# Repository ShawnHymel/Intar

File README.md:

Intar
=====

Open source laser tag system.

Repository Contents
-------------------

* **/Hardware** - Eagle design files (.brd, .sch)
* **/Libraries** - Libraries for use with the ZX Distance and Gesture Sensor

Documentation
-------------

Version History
---------------

* [H_0.0_L_0.2.0](https://github.com/ShawnHymel/Intar/tree/H_0.0_L_0.2.0) - Added ATtiny84 support to library
* [H_0.0_L_0.1.0](https://github.com/ShawnHymel/Intar/tree/H_0.0_L_0.1.0) - First prototype of a working IR library

License Information
-------------------

This product is _**open source**_! 

Please review the LICENSE.md file for license information. 

Distributed as-is; no warranty is given.

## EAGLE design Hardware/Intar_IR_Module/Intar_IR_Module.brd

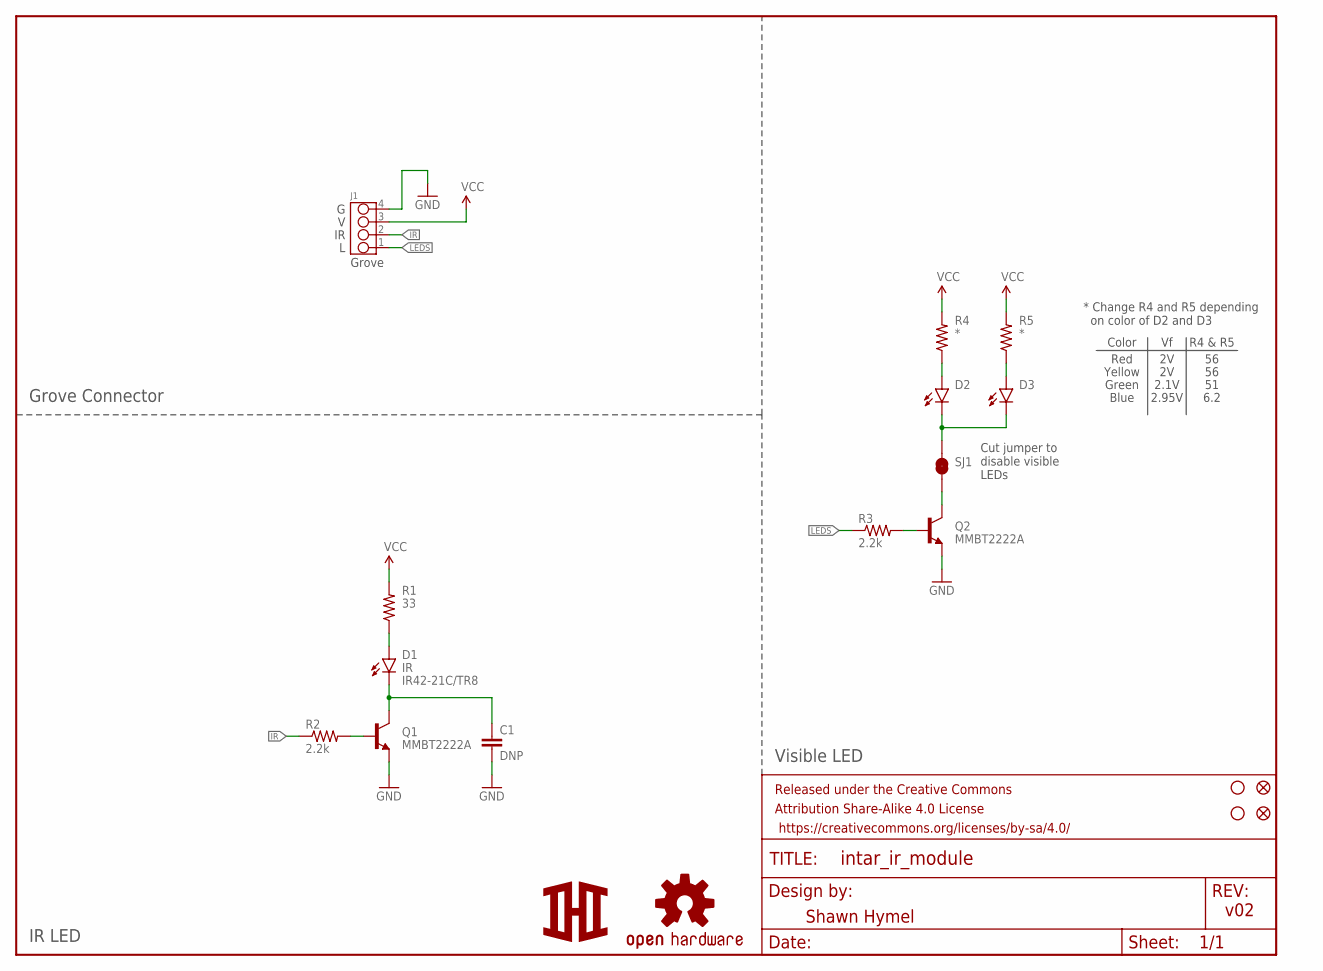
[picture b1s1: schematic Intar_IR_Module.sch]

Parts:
C1: DNP; 0603-CAP
D1: IR; IR42-21C/TR8
D2, D3: LED0603; LED-0603
FID1, FID2: FIDUCIAL1X2; FIDUCIAL-1X2
FRAME1: FRAME-LETTER; CREATIVE_COMMONS
J1: GROVE-4P-2.0-3470130P1; 4P-2.0
LOGO1: OSHW-LOGOS; OSHW-LOGO-S
Q1, Q2: MMBT2222A; SOT23-3
R1: 33; 0603-RES
R2, R3: 2.2k; 0603-RES
R4, R5: *; 0603-RES
SJ1: JUMPER-PAD-2-NC_BY_TRACE; PAD-JUMPER-2-NC_BY_TRACE_YES_SILK
STANDOFF1, STANDOFF2: STAND-OFF
U$1: LOGOSM; LOGO_SM

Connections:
GND: C1.2, J1.4, Q1.2 (E), Q2.2 (E)
IR: J1.2, R2.1
LEDS: J1.1, R3.1
unnamed: Q1.1 (B), R2.2
unnamed: D1.A, R1.1
unnamed: C1.1, D1.C, Q1.3 (C)
unnamed: D2.C, D3.C, SJ1.2
unnamed: Q2.1 (B), R3.2
unnamed: D2.A, R4.1
unnamed: D3.A, R5.1
unnamed: Q2.3 (C), SJ1.1
VCC: J1.3, R1.2, R4.2, R5.2

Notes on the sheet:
Shawn Hymel
v02
Grove
Cut jumper to disable visible LEDs
* Change R4 and R5 depending on color of D2 and D3
Color
R4 & R5
Red
Grove Connector
IR LED
Visible LED
Yellow
Green
2.1V
Blue
2.95V
6.2

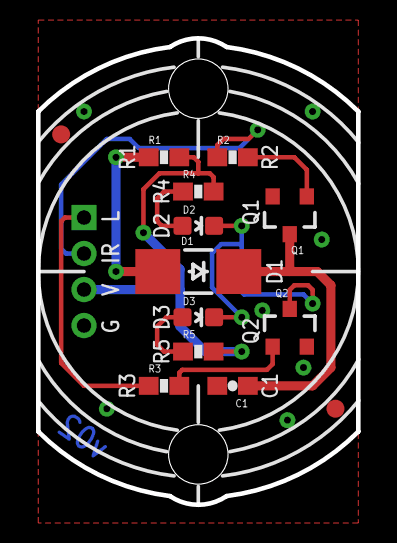
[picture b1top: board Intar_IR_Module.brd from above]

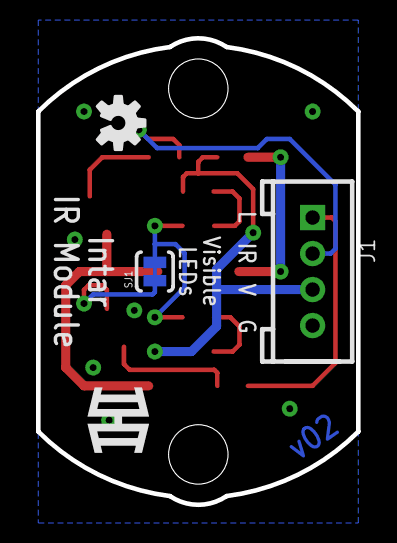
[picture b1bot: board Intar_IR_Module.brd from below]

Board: 2 copper layers, 17.8 x 25.9 mm, 20 parts (4 on the bottom side), 12 nets.

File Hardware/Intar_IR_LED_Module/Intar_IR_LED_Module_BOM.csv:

"Qty";"Value";"Device";"Package";"Parts";"Description";"MFG_NAME";"PROD_ID";"VALUE";
"2";"";"LED0603";"LED-0603";"D2, D3";"LEDs";"";"";"";
"2";"*";"RESISTOR0603-RES";"0603-RES";"R4, R5";"Resistor";"";"";"";
"1";"10nF";"10NF/10000PF-50V-10%(0603)";"0603-CAP";"C1";"CAP-00867";"";"CAP-00867";"10nF";
"2";"2.2k";"2.2KOHM-1/10W-1%(0603)";"0603-RES";"R2, R3";"RES-08272";"";"RES-08272";"2.2k";
"1";"30?";"RESISTOR0603-RES";"0603-RES";"R1";"Resistor";"";"";"";
"2";"FIDUCIAL1X2";"FIDUCIAL1X2";"FIDUCIAL-1X2";"FID1, FID2";"Fiducial Alignment Points";"";"";"";
"1";"FRAME-LETTER";"FRAME-LETTER";"CREATIVE_COMMONS";"FRAME1";"Schematic Frame";"";"";"";
"1";"GROVE-4P-2.0-3470130P1";"GROVE-4P-2.0-3470130P1";"4P-2.0";"J1";"";"";"";"";
"1";"IR";"LEDIR42-21C/TR8";"IR42-21C/TR8";"D1";"";"IR42-21C/TR8";"";"";
"1";"JUMPER-PAD-2-NC_BY_TRACE";"JUMPER-PAD-2-NC_BY_TRACE";"PAD-JUMPER-2-NC_BY_TRACE_YES_SILK";"SJ1";"";"";"";"";
"2";"MMBT2222A";"TRANSISTOR_NPNMMBT2222A";"SOT23-3";"Q1, Q2";"Generic NPN BJT";"";"TRANS-08049";"MMBT2222A";
"1";"OSHW-LOGOS";"OSHW-LOGOS";"OSHW-LOGO-S";"LOGO1";"Open Source Hardware Logo";"";"";"";
"2";"STAND-OFF";"STAND-OFF";"STAND-OFF";"STANDOFF1, STANDOFF2";"#4 Stand Off";"";"";"";

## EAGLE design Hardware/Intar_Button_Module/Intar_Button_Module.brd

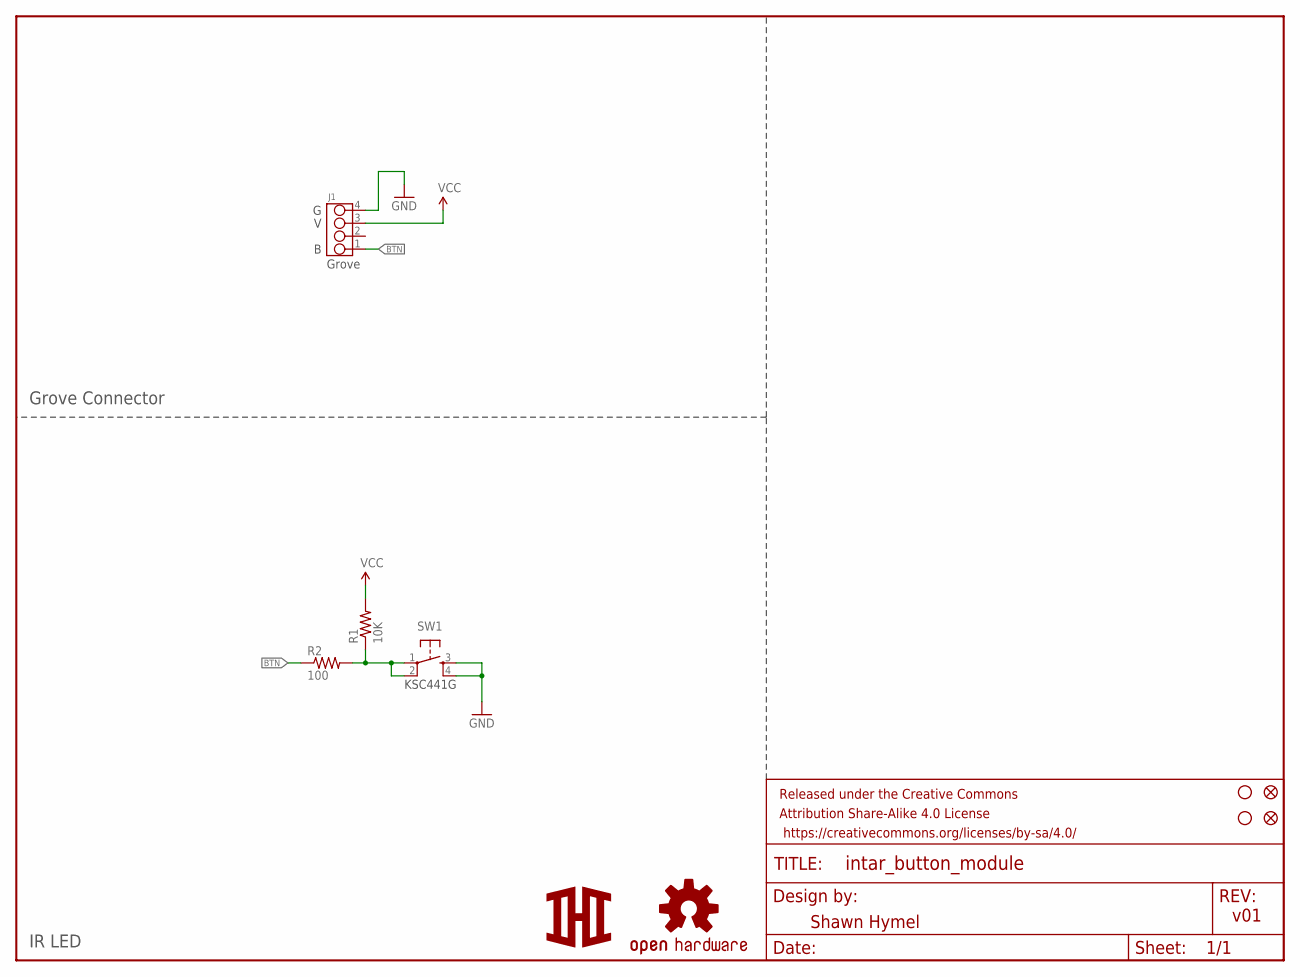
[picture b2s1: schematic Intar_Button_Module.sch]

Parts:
FID1, FID2: FIDUCIAL1X2; FIDUCIAL-1X2
FRAME1: FRAME-LETTER; CREATIVE_COMMONS
J1: GROVE-4P-2.0-3470130P1; 4P-2.0
LOGO1: OSHW-LOGOS; OSHW-LOGO-S
R1: 10K; 0603-RES
R2: 100; 0603-RES
STANDOFF1, STANDOFF2: STAND-OFF
SW1: SWITCH_MOMENTARY; KSCXXXG
U$1: LOGOSM; LOGO_SM

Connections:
BTN: J1.1, R2.1
GND: J1.4, SW1.3, SW1.4
unnamed: R1.1, R2.2, SW1.1, SW1.2
VCC: J1.3, R1.2

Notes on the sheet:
Shawn Hymel
v01
Grove
KSC441G
Grove Connector
IR LED

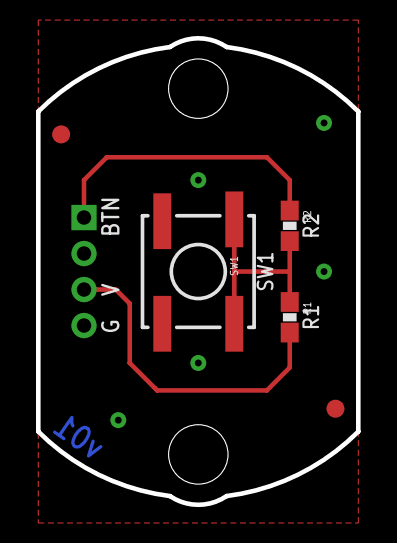
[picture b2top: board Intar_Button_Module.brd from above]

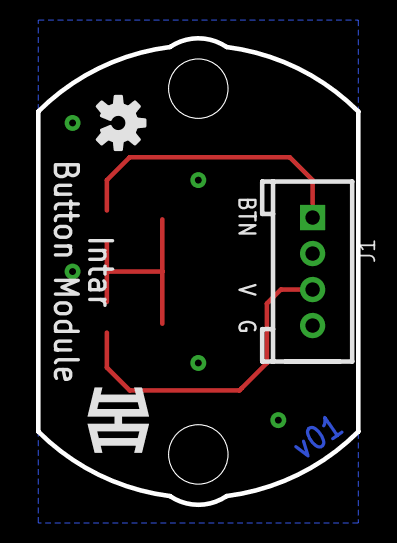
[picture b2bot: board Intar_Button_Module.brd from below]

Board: 2 copper layers, 17.8 x 25.9 mm, 11 parts (3 on the bottom side), 4 nets.

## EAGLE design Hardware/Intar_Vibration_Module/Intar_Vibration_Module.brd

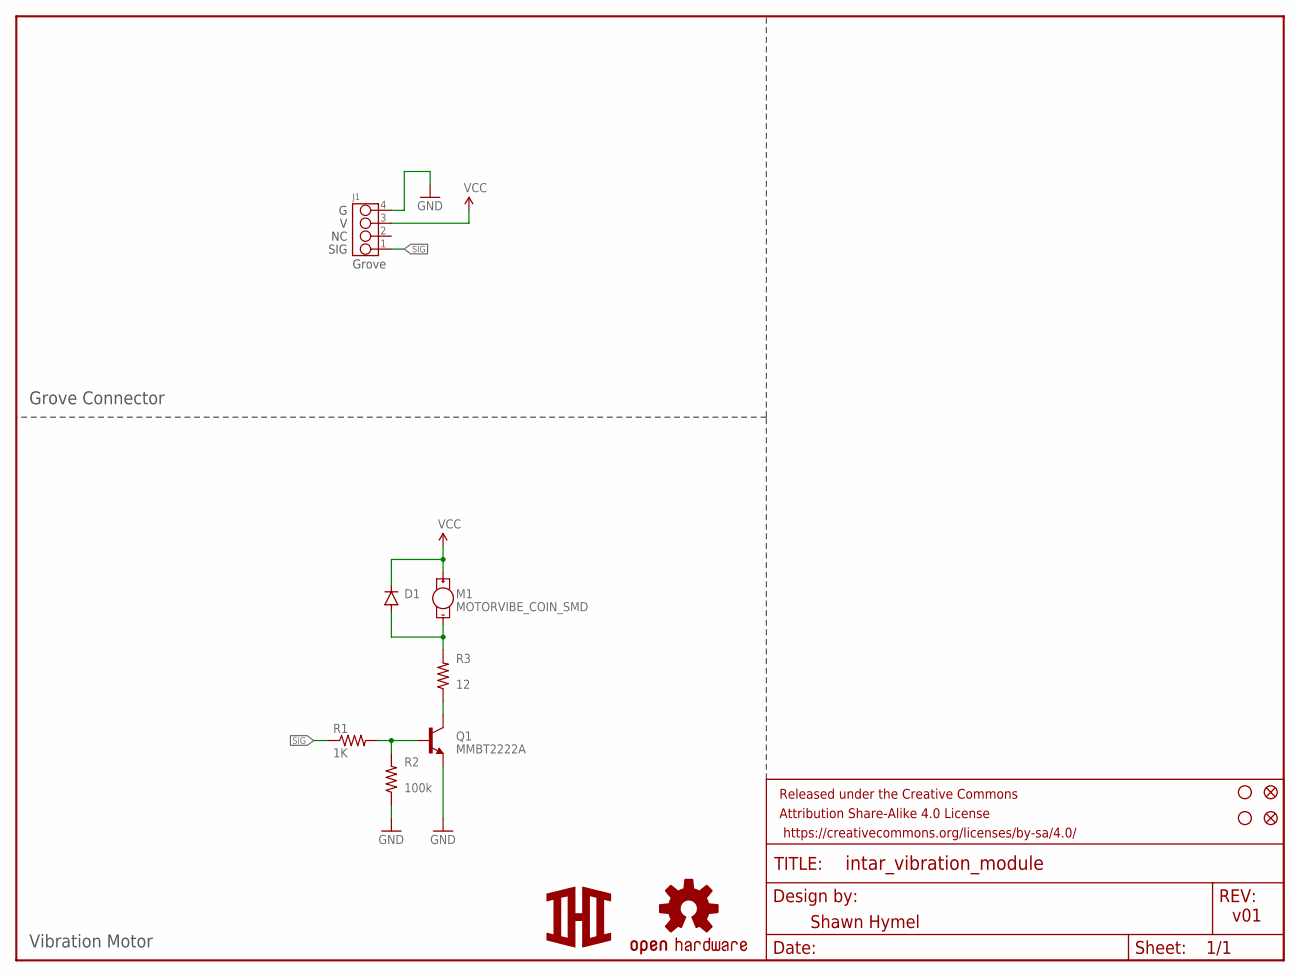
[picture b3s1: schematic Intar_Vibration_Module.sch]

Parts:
D1: 250mA/100V; SOD-323
FID1, FID2: FIDUCIAL1X2; FIDUCIAL-1X2
FRAME1: FRAME-LETTER; CREATIVE_COMMONS
J1: GROVE-4P-2.0-3470130P1; 4P-2.0
LOGO1: OSHW-LOGOS; OSHW-LOGO-S
M1: MOTORVIBE_COIN_SMD; VIBE_COIN_SMD
Q1: MMBT2222A; SOT23-3
R1: 1K; 0603-RES
R2: 100k; 0603-RES
R3: 12; 0603-RES
STANDOFF1, STANDOFF2: STAND-OFF
U$1: LOGOSM; LOGO_SM

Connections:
GND: J1.4, Q1.2 (E), R2.1
unnamed: Q1.1 (B), R1.2, R2.2
unnamed: Q1.3 (C), R3.1
unnamed: D1.A, M1.2 (-), R3.2
SIG: J1.1, R1.1
VCC: D1.C, J1.3, M1.1 (+)

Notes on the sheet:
Shawn Hymel
v01
Grove
Grove Connector
Vibration Motor
SIG

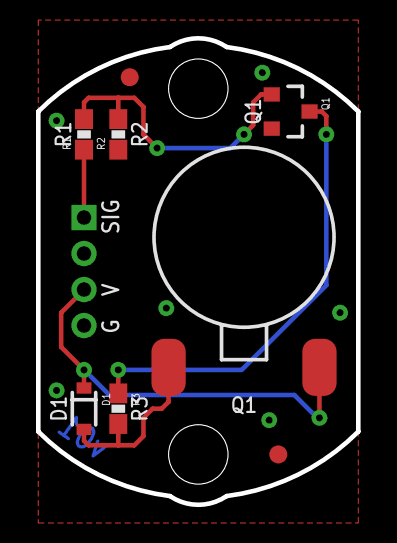
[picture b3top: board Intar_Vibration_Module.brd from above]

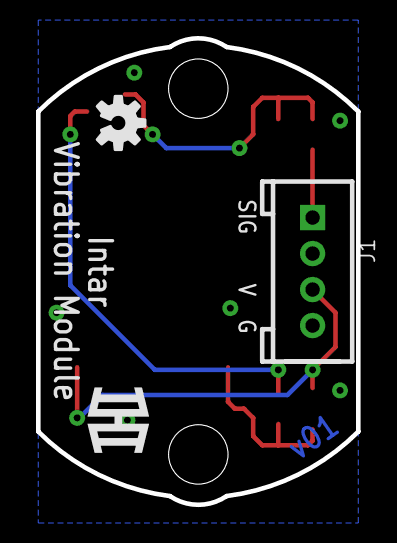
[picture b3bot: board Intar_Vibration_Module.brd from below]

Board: 2 copper layers, 17.8 x 25.9 mm, 14 parts (3 on the bottom side), 6 nets.

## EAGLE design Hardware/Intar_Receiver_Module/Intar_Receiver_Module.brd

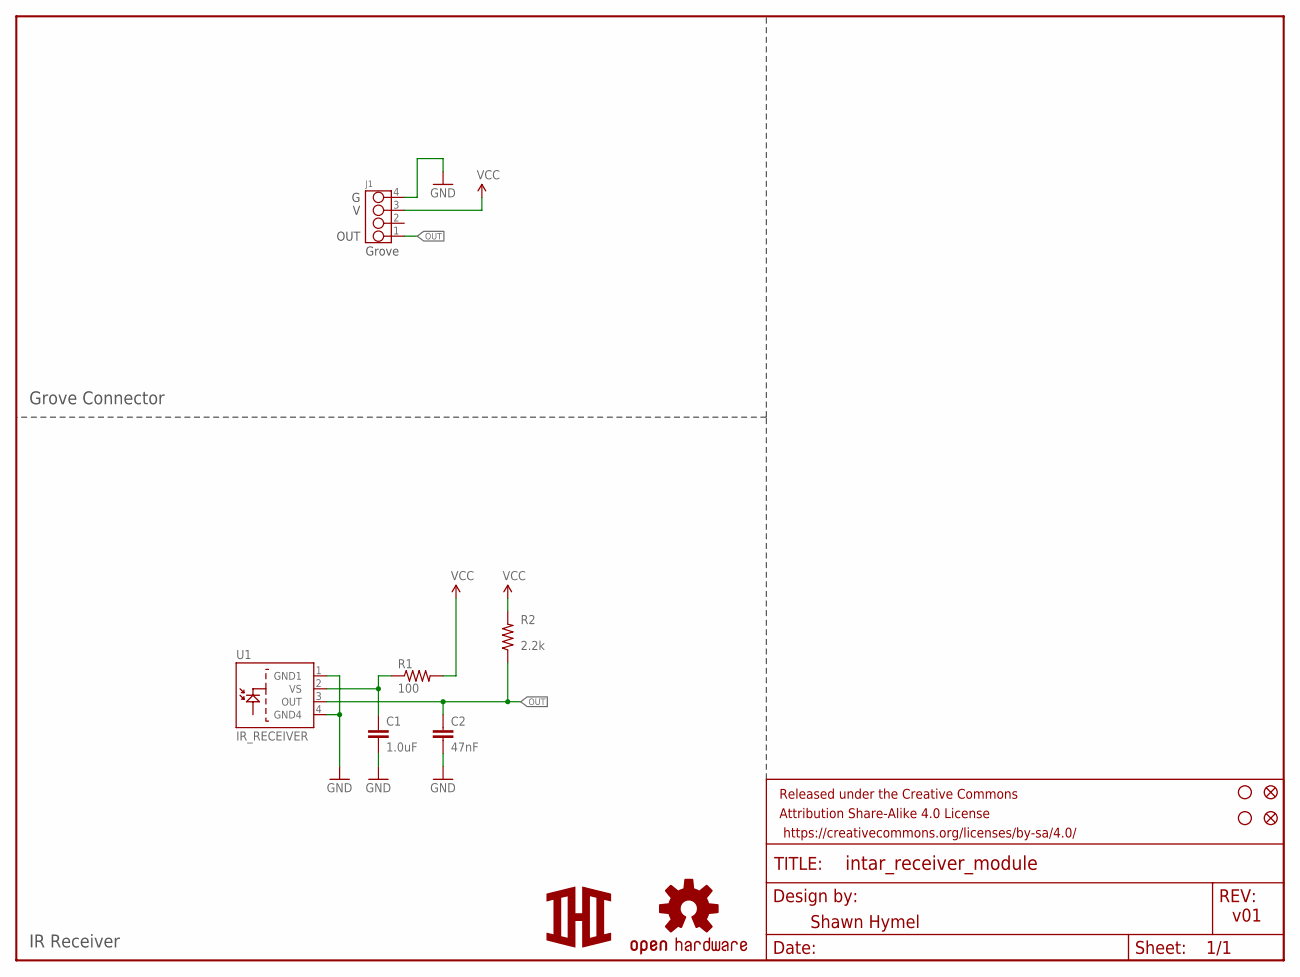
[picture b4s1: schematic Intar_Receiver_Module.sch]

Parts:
C1: 1.0uF; 0603-CAP
C2: 47nF; 0603-CAP
FID1, FID2: FIDUCIAL1X2; FIDUCIAL-1X2
FRAME1: FRAME-LETTER; CREATIVE_COMMONS
J1: GROVE-4P-2.0-3470130P1; 4P-2.0
LOGO1: OSHW-LOGOS; OSHW-LOGO-S
R1: 100; 0603-RES
R2: 2.2k; 0603-RES
STANDOFF1, STANDOFF2: STAND-OFF
U1: IR_RECEIVER; TSOP754XXW
U$1: LOGOSM; LOGO_SM

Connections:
GND: C1.2, C2.2, J1.4, U1.1 (GND1), U1.4 (GND4)
unnamed: C1.1, R1.1, U1.2 (VS)
OUT: C2.1, J1.1, R2.1, U1.3 (OUT)
VCC: J1.3, R1.2, R2.2

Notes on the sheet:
Shawn Hymel
v01
Grove
Grove Connector
IR Receiver
OUT

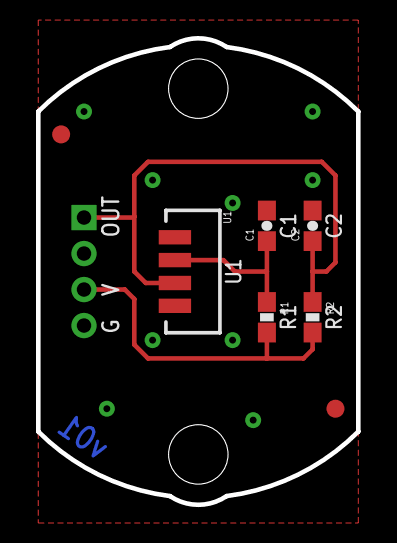
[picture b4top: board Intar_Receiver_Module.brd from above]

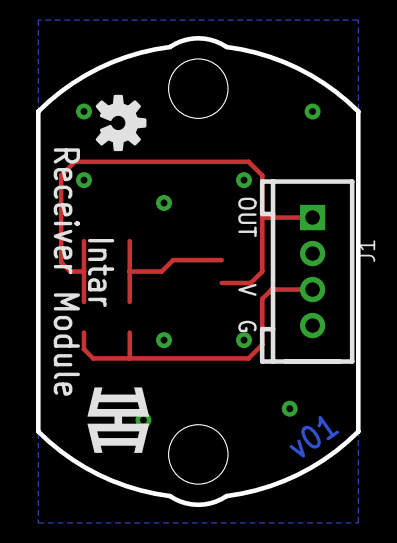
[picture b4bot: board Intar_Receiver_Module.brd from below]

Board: 2 copper layers, 17.8 x 25.9 mm, 13 parts (3 on the bottom side), 4 nets.

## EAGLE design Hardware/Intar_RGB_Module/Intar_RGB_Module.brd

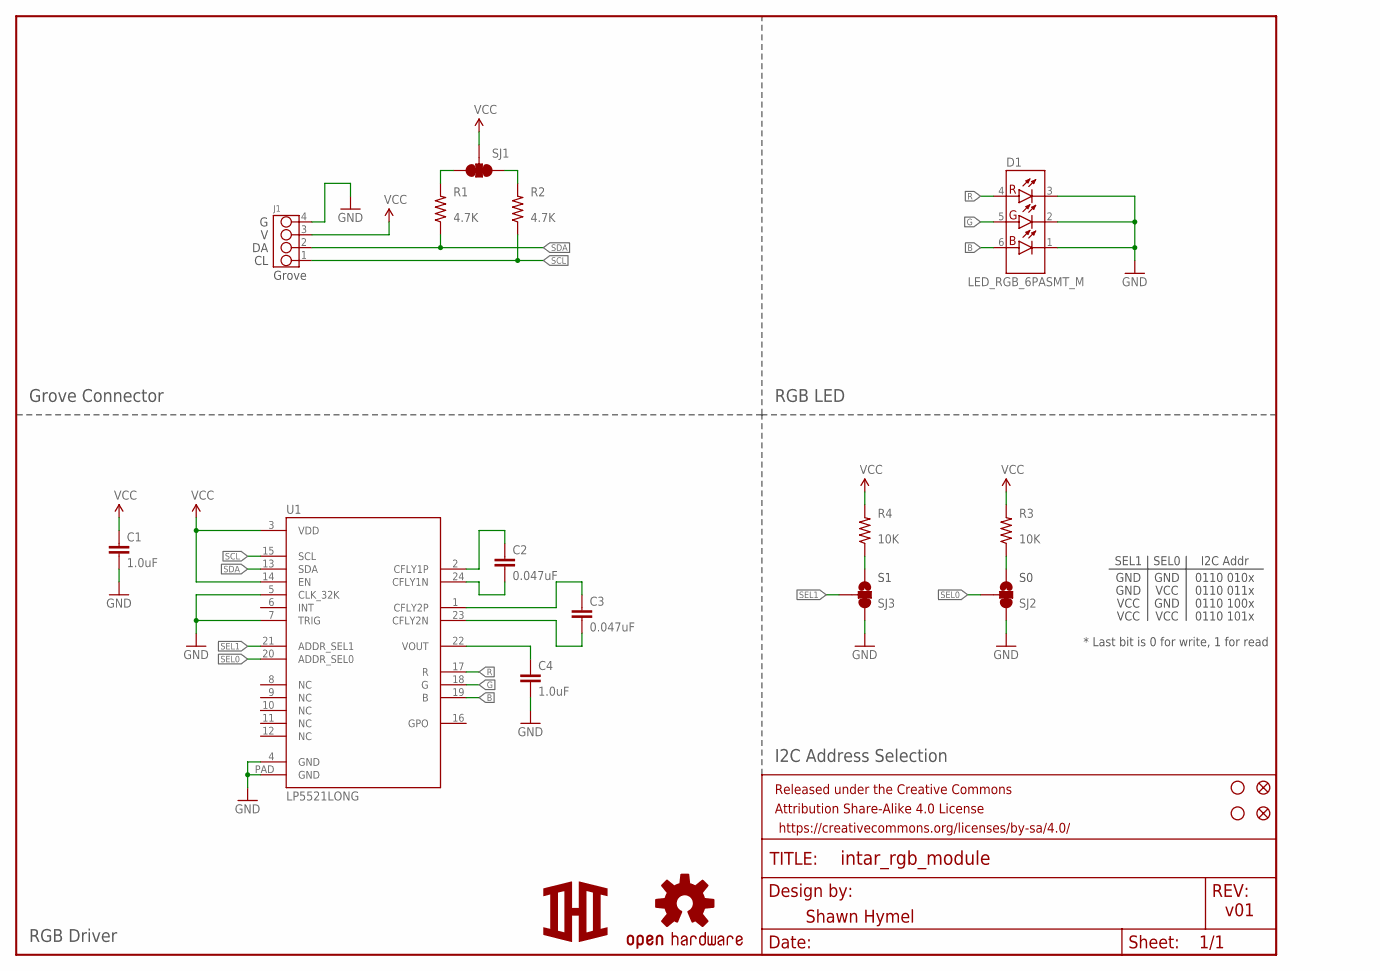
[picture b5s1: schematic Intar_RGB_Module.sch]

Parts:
C1, C4: 1.0uF; 0603-CAP
C2, C3: 0.047uF; 0603-CAP
D1: LED_RGB_6PASMT_M; ASMT-YTB7-0AA02_M
FID1, FID2: FIDUCIAL1X2; FIDUCIAL-1X2
FRAME1: FRAME-LETTER; CREATIVE_COMMONS
J1: GROVE-4P-2.0-3470130P1; 4P-2.0
LOGO1: OSHW-LOGOS; OSHW-LOGO-S
R1, R2: 4.7K; 0603-RES
R3, R4: 10K; 0603-RES
SJ1: SOLDERJUMPER_2WAYPASTE1&2&3; SJ_3_PASTE1&2&3
SJ2, SJ3: SOLDERJUMPER_2WAYPASTE2&3; SJ_3_PASTE2&3
STANDOFF1, STANDOFF2: STAND-OFF
U1: LP5521LONG; WQFN-24_LONG
U$1: LOGOSM; LOGO_SM

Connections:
B: D1.6 (B_A), U1.19 (B)
G: D1.5 (G_A), U1.18 (G)
GND: C1.2, C4.2, D1.1 (B_C), D1.2 (G_C), D1.3 (R_C), J1.4, SJ2.3, SJ3.3, U1.4 (GND), U1.5 (CLK_32K), U1.7 (TRIG), U1.PAD (GND)
unnamed: C2.1, U1.2 (CFLY1P)
unnamed: C2.2, U1.24 (CFLY1N)
unnamed: C3.1, U1.1 (CFLY2P)
unnamed: C3.2, U1.23 (CFLY2N)
unnamed: C4.1, U1.22 (VOUT)
unnamed: R1.2, SJ1.3
unnamed: R2.2, SJ1.1
unnamed: R3.1, SJ2.1
unnamed: R4.1, SJ3.1
R: D1.4 (R_A), U1.17 (R)
SCL: J1.1, R2.1, U1.15 (SCL)
SDA: J1.2, R1.1, U1.13 (SDA)
SEL0: SJ2.2, U1.20 (ADDR_SEL0)
SEL1: SJ3.2, U1.21 (ADDR_SEL1)
VCC: C1.1, J1.3, R3.2, R4.2, SJ1.2, U1.3 (VDD), U1.14 (EN)

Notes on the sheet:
Shawn Hymel
v01
Grove
Grove Connector
RGB Driver
I2C Address Selection
RGB LED
* Last bit is 0 for write, 1 for read
SEL1
SEL0
I2C Addr
GND
0110 010x
VCC
0110 011x
0110 100x
0110 101x

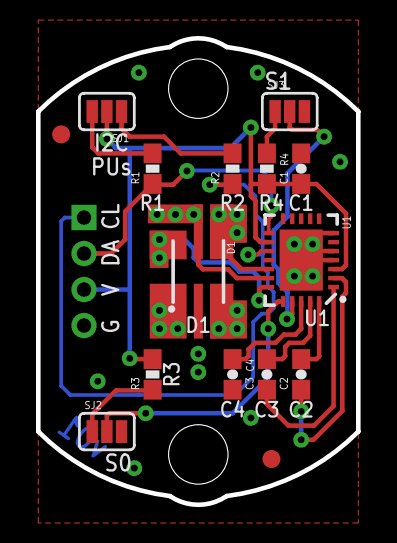
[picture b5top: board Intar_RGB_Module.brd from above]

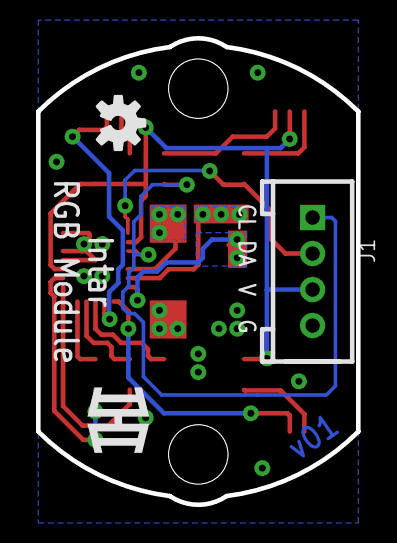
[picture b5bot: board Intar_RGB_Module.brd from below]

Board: 2 copper layers, 17.8 x 25.9 mm, 21 parts (3 on the bottom side), 18 nets.

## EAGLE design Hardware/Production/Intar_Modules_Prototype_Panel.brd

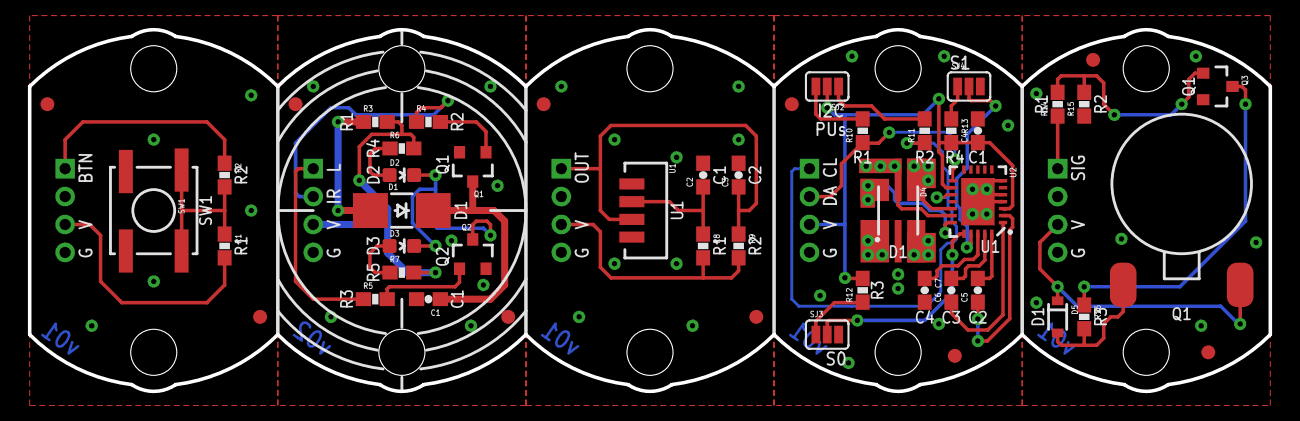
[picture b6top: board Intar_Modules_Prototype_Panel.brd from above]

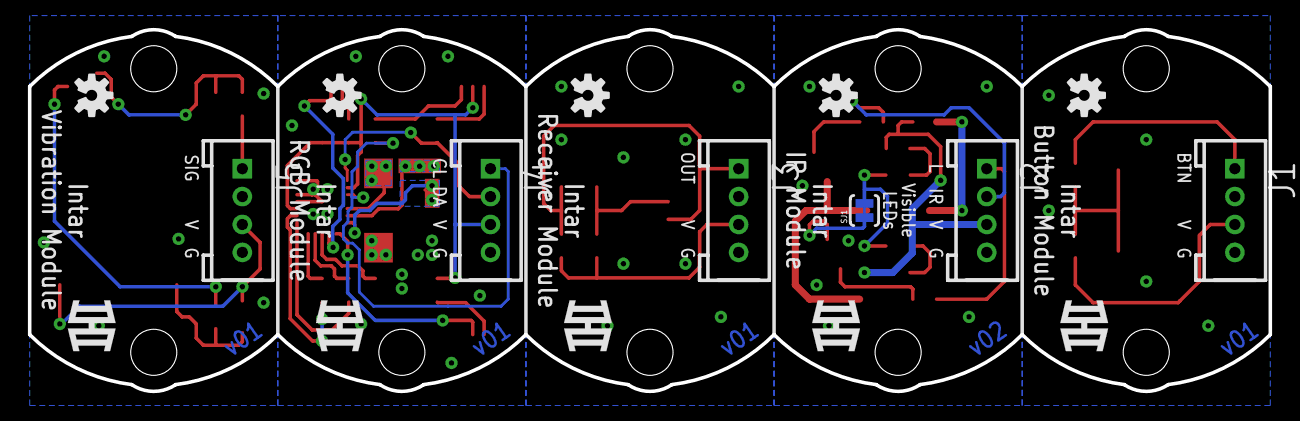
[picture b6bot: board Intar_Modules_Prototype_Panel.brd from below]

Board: 2 copper layers, 88.9 x 25.9 mm, 74 parts (16 on the bottom side), 44 nets.

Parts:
C1: DNP; 0603-CAP
C2, C4, C7: 1.0uF; 0603-CAP
C3: 47nF; 0603-CAP
C5, C6: 0.047uF; 0603-CAP
D1: IR; IR42-21C/TR8
D2, D3: LED-0603
D4: LED_RGB_6PASMT_M; ASMT-YTB7-0AA02_M
D5: 250mA/100V; SOD-323
FID1, FID2, FID3, FID4, FID5, FID6, FID7, FID8, FID9, FID10: FIDUCIAL1X2; FIDUCIAL-1X2
J1, J2, J3, J4, J5: GROVE-4P-2.0-3470130P1; 4P-2.0
LOGO1, LOGO2, LOGO3, LOGO4, LOGO5: OSHW-LOGOS; OSHW-LOGO-S
M1: MOTORVIBE_COIN_SMD; VIBE_COIN_SMD
Q1, Q2, Q3: MMBT2222A; SOT23-3
R1, R12, R13: 10K; 0603-RES
R2, R8: 100; 0603-RES
R3: 33; 0603-RES
R4, R5, R9: 2.2k; 0603-RES
R6, R7: *; 0603-RES
R10, R11: 4.7K; 0603-RES
R14: 1K; 0603-RES
R15: 100k; 0603-RES
R16: 12; 0603-RES
SJ1: JUMPER-PAD-2-NC_BY_TRACE; PAD-JUMPER-2-NC_BY_TRACE_YES_SILK
SJ2: SJ_3_PASTE1&2&3
SJ3, SJ4: SJ_3_PASTE2&3
STANDOFF1, STANDOFF2, STANDOFF3, STANDOFF4, STANDOFF5, STANDOFF6, STANDOFF7, STANDOFF8, STANDOFF9, STANDOFF10: STAND-OFF
SW1: SWITCH_MOMENTARY; KSCXXXG
U1: IR_RECEIVER; TSOP754XXW
U2: LP5521LONG; WQFN-24_LONG
U$1, U$2, U$3, U$4, U$5: LOGOSM; LOGO_SM

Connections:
B: D4.6, U2.19
BTN: J1.1, R2.1
G: D4.5, U2.18
GND: J1.4, SW1.3, SW1.4
GND1: C1.2, J2.4, Q1.2, Q2.2
GND2: C2.2, C3.2, J3.4, U1.1, U1.4
GND3: C4.2, C7.2, D4.1, D4.2, D4.3, J4.4, SJ3.3, SJ4.3, U2.4, U2.5, U2.7, U2.PAD
GND4: J5.4, Q3.2, R15.1
IR: J2.2, R4.1
LEDS: J2.1, R5.1
unnamed: R1.1, R2.2, SW1.1, SW1.2
unnamed: Q1.1, R4.2
unnamed: D1.A, R3.1
unnamed: C1.1, D1.C, Q1.3
unnamed: Q2.1, R5.2
unnamed: D2.A, R6.1
unnamed: D2.C, D3.C, SJ1.2
unnamed: D3.A, R7.1
unnamed: Q2.3, SJ1.1
unnamed: C2.1, R8.1, U1.2
unnamed: C5.1, U2.2
unnamed: C5.2, U2.24
unnamed: C6.1, U2.1
unnamed: C6.2, U2.23
unnamed: C7.1, U2.22
unnamed: R10.2, SJ2.3
unnamed: R11.2, SJ2.1
unnamed: R12.1, SJ3.1
unnamed: R13.1, SJ4.1
unnamed: Q3.1, R14.2, R15.2
unnamed: Q3.3, R16.1
unnamed: D5.A, M1.2, R16.2
OUT: C3.1, J3.1, R9.1, U1.3
R: D4.4, U2.17
SCL: J4.1, R11.1, U2.15
SDA: J4.2, R10.1, U2.13
SEL0: SJ3.2, U2.20
SEL1: SJ4.2, U2.21
SIG: J5.1, R14.1
VCC: J1.3, R1.2
VCC1: J2.3, R3.2, R6.2, R7.2
VCC2: J3.3, R8.2, R9.2
VCC3: C4.1, J4.3, R12.2, R13.2, SJ2.2, U2.3, U2.14
VCC4: D5.C, J5.3, M1.1

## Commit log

2015-03-31 Initial commit with License.
2015-03-31 Created TagIR library template.
2015-04-01 Added template for class and interrupt constants.
2015-05-25 Added Teensy LC lines for timer interrupts.
2015-05-31 Trigger to LED working.
2015-06-02 Added 38 kHz modulation for Teensy LC.
2015-06-03 Changed OVF to COMP on 328p interrupt.
2015-06-03 Added transmit code.
2015-06-03 Fixed transmit for Teensy LC.
2015-06-11 Fixed SOM being too long.
2015-06-17 Added receiver framework. Need to add tick counter values to ring buffer.
2015-06-18 Added receiver. Not really working.
2015-07-14 Receiver implemented. 328p seems to have half-time ticks.
2015-07-15 Fixed error of getting stuck in RECV ERROR
2015-07-15 Changed IntarIR to IntarPhys (for 'Physical Layer'). IntarIR will become the wrapper class.
2015-07-16 Fixed issue with 328p interrupting twice as fast (420 did not fit in an 8-bit register. Derp.)
2015-07-16 Created wrapper class 'IntarIR' for IR comms. Created skeleton of IRDemo to play a simple tag game.
2015-07-17 Created simple game in IRDemo example. This shows how the IR transmit and receive works.
2015-07-17 Fixed HP and damage numbers in IRDemo info header.
2015-07-24 Finished IR LED Module and sent v01 to PCB fab
2015-07-25 Created BOM
2015-07-26 Removed Eagle library backup files and .csv BOM.
2015-07-27 Added barrel files for C-26A.
2015-07-27 Adding profiles and models
    Seburo C-26a.svg - Profiles for laser cutting the rifle
    Seburo_Testfit.skp - Sketchup model
    Seburo_Testfit_profiles.dxf - DXF profiles for testfitting NO SCREWHOLES
    NOT FINAL
2015-07-27 Updating Drawings
    3Ds, DXFs and SVGs for rifle updated for support of barrel components.
    SVGs for barrel components are not updated yet.
2015-07-29 Updated barrel design for C-26A
2015-07-31 Re-constructed board outline for IR LED Module.
2015-08-01 Updating SVG files to add trigger mechanism.
2015-08-01 Updating drawings for trigger assembly.
2015-08-04 Created LP5521 part
2015-08-05 Added RGB LED to library
2015-08-05 Started RGB module schematic
2015-08-05 Adding current project logo
2015-08-05 Imported logo into Eagle
2015-08-06 Created vibration motor part.
2015-08-07 Created schematics for first round of modules.
2015-08-08 Arranged components on all modules
2015-08-08 RGB layout almost done'
2015-08-10 Finished RGB and IR modules
2015-08-10 Fixed Grove connectors to be right way (pin 4 should be GND)
2015-08-11 Button module layout done.
2015-08-11 Completed Vibration Module v01 layout
2015-08-11 Moved IHI and OSH logos away from name on all boards.
2015-08-11 Added silly circle silk to IR Module.
2015-08-11 Adjusted via in IR module
2015-08-11 Proto production panel created for Modules
2015-08-11 Created gerbers for modules panel (prototype v01)
2015-08-30 Mechanical Drawings Update! Removed outdated profiles so that all of the drawings are now compiled, complete and accurate.
2015-08-30 Seburo C-26a profiles are laser ready and arranged for 24x18 cutting bed.
2015-09-09 Created BOM for button module.
2015-09-11 Created BOM for the rest of the modules
2016-12-09 Added ATtiny84 support. Seems to have issues transmitting: pulse() is skipped in state machine.
2016-12-13 Actually committing ATtiny84 fixes
2016-12-14 Added support for ATTiny84. Made flushTransmitter a public function. Added SoftwareSerial support for examples.

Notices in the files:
parts and their libraries:
SparkFun-Aesthetics: Licensing: Creative Commons ShareAlike 4.0 International - https://creativecommons.org/licenses/by-sa/4.0
SparkFun-Aesthetics: Released under the Creative Commons Attribution Share-Alike 4.0 License
SparkFun-Aesthetics: https://creativecommons.org/licenses/by-sa/4.0
